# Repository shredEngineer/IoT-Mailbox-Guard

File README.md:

# IoT mailbox guard

For complete project description, parts list and links to related resources, see:

https://paulwilhelm.de/briefkastenwaechter/

https://www.hackster.io/shredengineer/iot-mailbox-guard-ab33c1

## Schematic

## Board

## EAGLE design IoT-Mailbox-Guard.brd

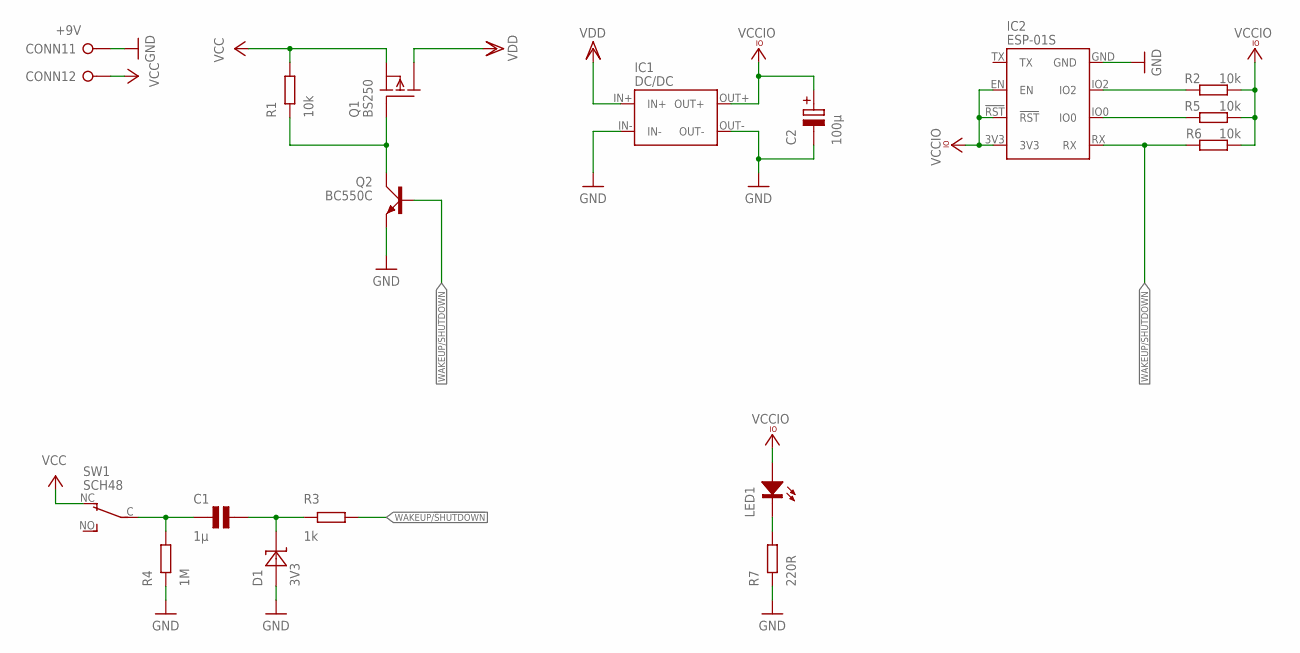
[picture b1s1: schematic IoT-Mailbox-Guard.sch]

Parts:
C1: 1µ; GENERIC-5.08
C2: 100µ; ELKO-2.54-6MM
CONN1: +9V; WAGO-2
D1: 3V3; DIODE-7.62
IC1: DC/DC; DC/DC-MINI360-BUCK
IC2: ESP-01S
LED1: LED-3
Q1: BS250; TO-92
Q2: BC550C; TO-92
R1, R2, R5, R6: 10k; GENERIC-7.62
R3: 1k; GENERIC-7.62
R4: 1M; GENERIC-7.62
R7: 220R; GENERIC-7.62
SW1: SCH48; MICROSWITCH-SCH48

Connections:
GND: C2.-, CONN1.1, D1.A, IC1.IN-, IC1.OUT-, IC2.GND, Q2.3 (E), R4.1, R7.1
unnamed: C1.1, R4.2, SW1.C (COM)
unnamed: C1.2, D1.C, R3.1
unnamed: LED1.K (C), R7.2
unnamed: IC2.IO2, R2.1
unnamed: IC2.IO0, R5.1
SHUTDOWN_PULSE: Q1.2 (G), Q2.1 (C), R1.1
VCC: CONN1.2, Q1.3 (S), R1.2, SW1.NC
VCCIO: C2.+, IC1.OUT+, IC2.3V3, IC2.!RST, IC2.EN, LED1.A, R2.2, R5.2, R6.2
VDD: IC1.IN+, Q1.1 (D)
WAKEUP/!SHUTDOWN: IC2.RX, Q2.2 (B), R3.2, R6.1

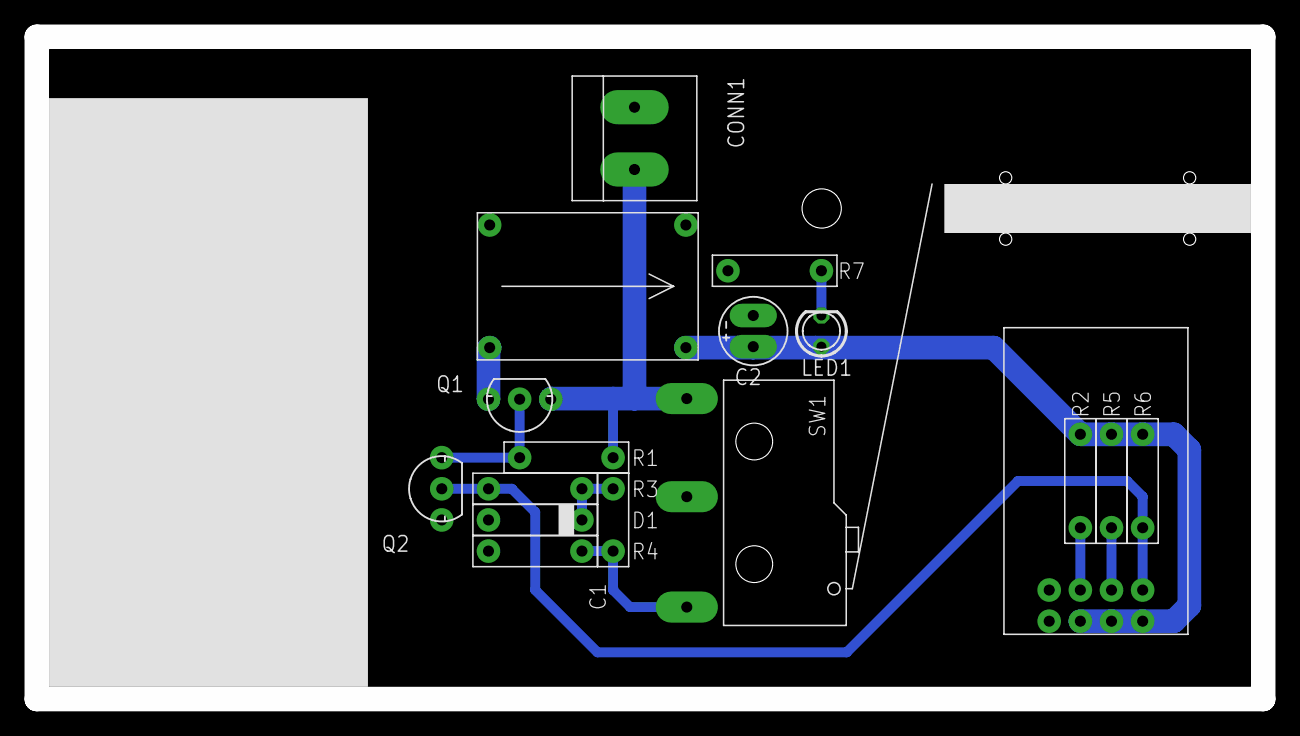
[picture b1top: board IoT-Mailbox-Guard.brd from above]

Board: 2 copper layers, 100.0 x 54.0 mm, 17 parts (0 on the bottom side), 11 nets.

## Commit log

2021-01-31 Create LICENSE
